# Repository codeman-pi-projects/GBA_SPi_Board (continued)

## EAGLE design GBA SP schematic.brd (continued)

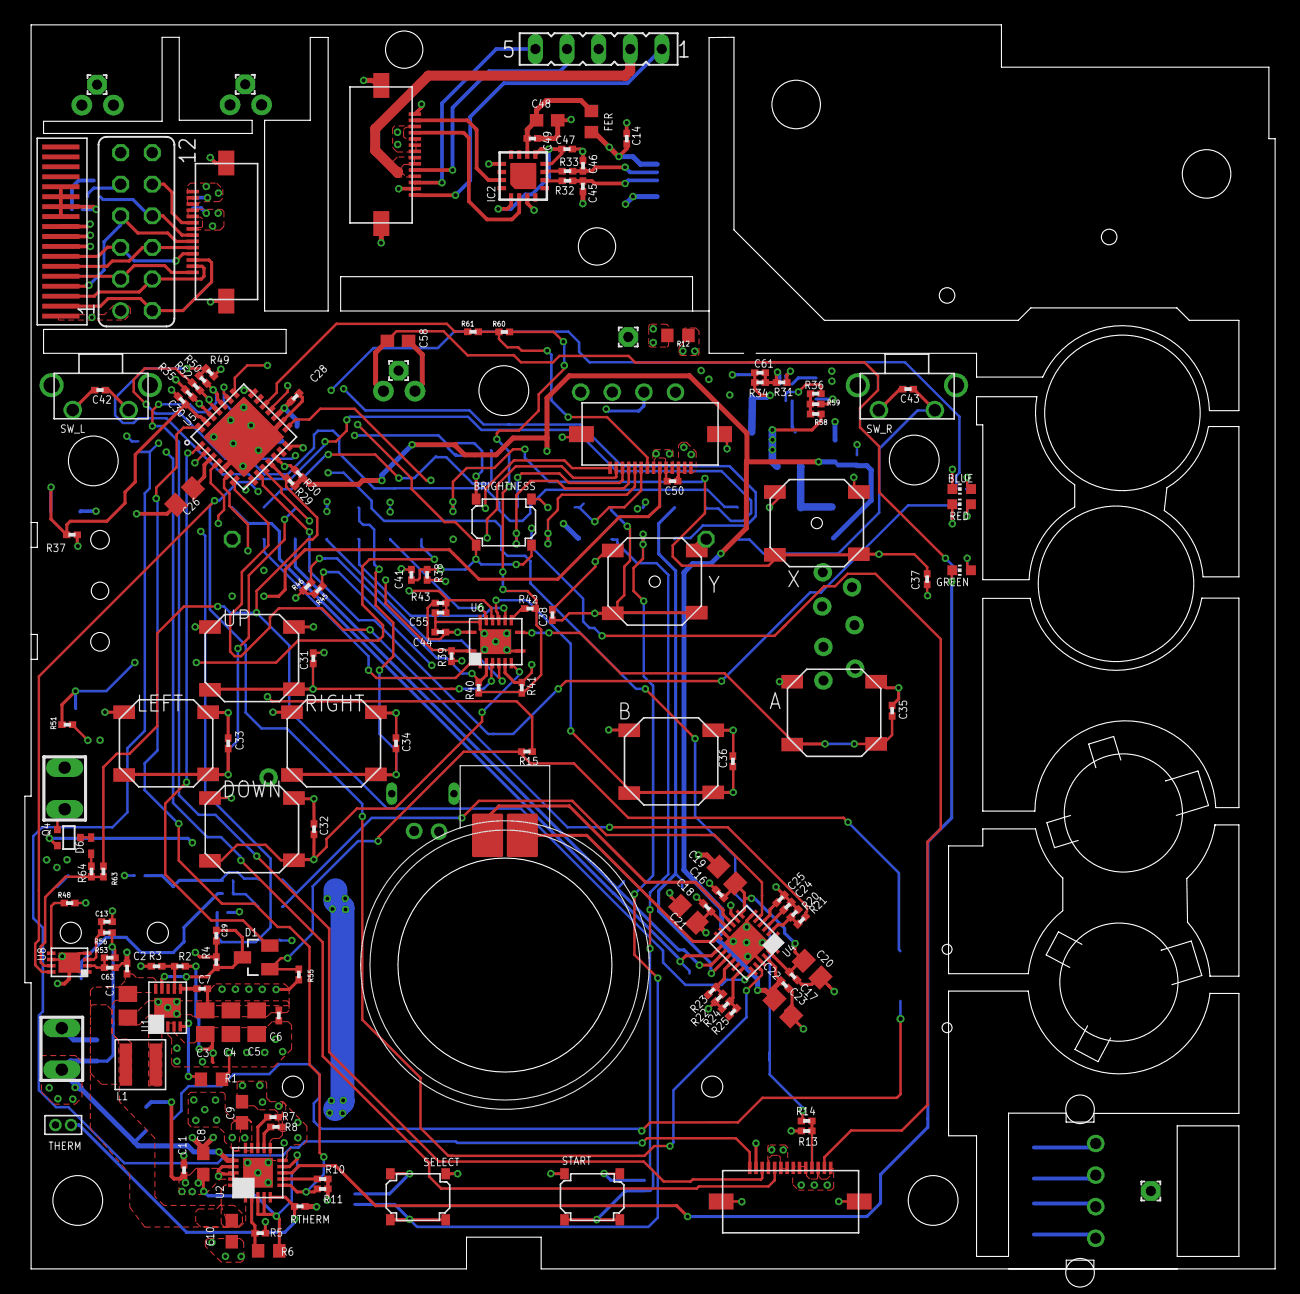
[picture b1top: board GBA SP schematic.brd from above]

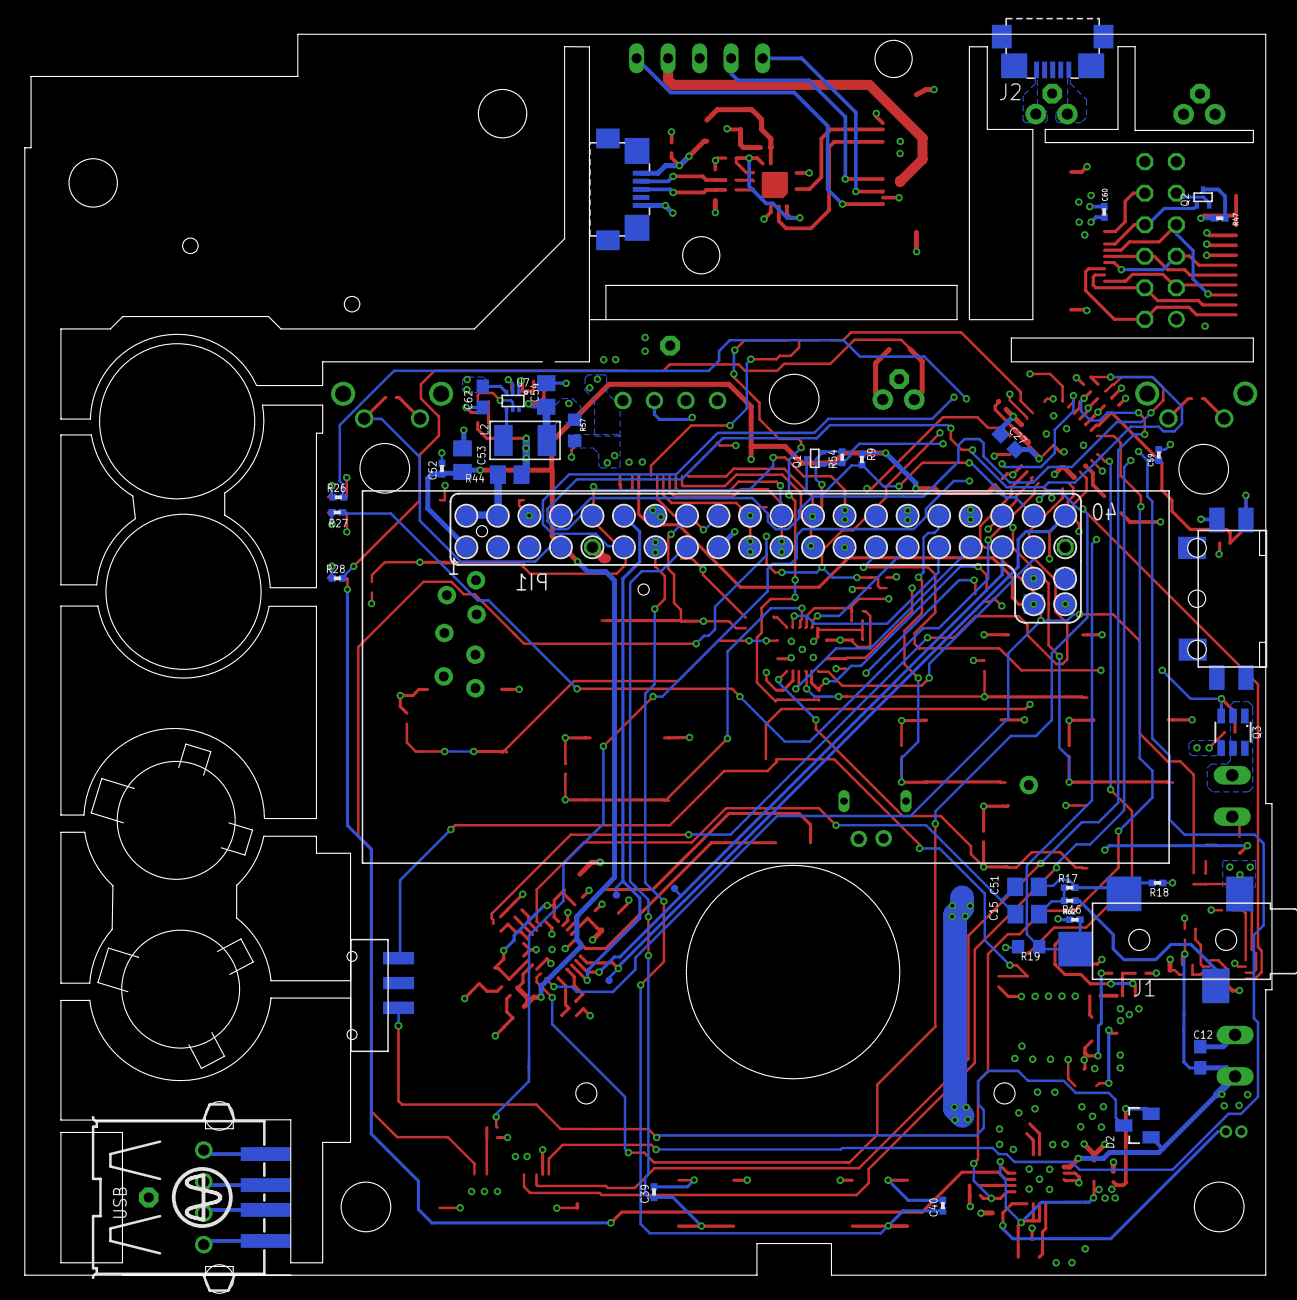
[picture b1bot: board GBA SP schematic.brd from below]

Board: 4 copper layers, 100.5 x 100.0 mm, 191 parts (40 on the bottom side), 139 nets.

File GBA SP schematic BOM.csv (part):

"Part";"Value";"Device";"Package";"Description";"DIGIKEY";"MF";"MOUSER";"MPN";"OC_FARNELL";"OC_NEWARK";"TP_SIGNAL_NAME";
"A";"TACTILEGBA_SP";"TACTILEGBA_SP";"GBA_SP_TACT";"";"";"ALPS";"";"SKRRAAE010";"";"";"";
"B";"TACTILEGBA_SP";"TACTILEGBA_SP";"GBA_SP_TACT";"";"";"ALPS";"688-SKRRAA";"SKRRAAE010";"";"";"";
"BATT";"DNP";"HEADER-1X2";"HEADER-1X2";"";"";"";"";"";"";"";"";
"BLUE";"";"LEDCHIP-LED0603";"CHIP-LED0603";"LED";"160-1827-1-ND";"Lite-On";"";"LTST-C193TBKT-5A";"";"";"";
"BRIGHTNESS";"TACTILE";"TACTILE";"TL3315";"";"EG4621CT-ND";"E-switch";"";"TL3315NF160Q";"";"";"";
"C1";"22uF";"C-USC0805";"C0805";"CAPACITOR, American symbol";"587-5464-1-ND";"Taiyo Yuden";"";"LMK212BBJ226MG-T";"";"";"";
"C2";"0.1uF";"C-US0402_REAL";"0402_REAL";"CAPACITOR, American symbol";"311-1343-1-ND";"Yageo";"";"CC0603ZRY5V9BB104";"";"";"";
"C3";"22uF";"C-USC0805";"C0805";"CAPACITOR, American symbol";"587-5464-1-ND";"Taiyo Yuden";"";"LMK212BBJ226MG-T";"";"";"";
"C4";"22uF";"C-USC0805";"C0805";"CAPACITOR, American symbol";"587-5464-1-ND";"Taiyo Yuden";"";"LMK212BBJ226MG-T";"";"";"";
"C5";"22uF";"C-USC0805";"C0805";"CAPACITOR, American symbol";"587-5464-1-ND";"Taiyo Yuden";"";"LMK212BBJ226MG-T";"";"";"";
"C6";"0.1uF";"C-US0402_REAL";"0402_REAL";"CAPACITOR, American symbol";"311-1343-1-ND";"Yageo";"";"CC0603ZRY5V9BB104";"";"";"";
"C7";"10nF";"C-US0402_REAL";"0402_REAL";"CAPACITOR, American symbol";"490-4516-1-ND";"Murata";"";"GRM155R71H103KA88D";"";"";"";
"C8";"4.7uF";"C-EUC0603";"C0603";"CAPACITOR, European symbol";"311-1455-1-ND";"Yageo";"";"CC0603KRX5R6BB475";"";"";"";
"C9";"4.7uF";"C-EUC0603";"C0603";"CAPACITOR, European symbol";"311-1455-1-ND";"Yageo";"";"CC0603KRX5R6BB475";"";"";"";
"C10";"4.7uF";"C-EUC0603";"C0603";"CAPACITOR, European symbol";"311-1455-1-ND";"Yageo";"";"CC0603KRX5R6BB475";"";"";"";
"C11";"0.1uF";"C-US0402_REAL";"0402_REAL";"CAPACITOR, American symbol";"311-1343-1-ND";"Yageo";"";"CC0603ZRY5V9BB104";"";"";"";
"C12";"4.7uF";"C-EUC0603";"C0603";"CAPACITOR, European symbol";"311-1455-1-ND";"Yageo";"";"CC0603KRX5R6BB475";"";"";"";
"C13";"0.1uF";"C-US0402_REAL";"0402_REAL";"CAPACITOR, American symbol";"490-4516-1-ND";"Murata";"";"GRM155R71H103KA88D";"";"";"";
"C14";"0.1uF";"C-EU0402_REAL";"0402_REAL";"CAPACITOR, European symbol";"311-1343-1-ND";"Yageo";"";"CC0603ZRY5V9BB104";"";"";"";
"C15";"47uF";"C-EUC0805";"C0805";"CAPACITOR, European symbol";"490-9961-1-ND";"Murata";"";"GRM21BR61A476ME15L";"";"";"";
"C16";"0.1uF";"C-US0402_REAL";"0402_REAL";"CAPACITOR, American symbol";"311-1343-1-ND";"Yageo";"";"CC0603ZRY5V9BB104";"";"";"";
"C17";"0.1uF";"C-US0402_REAL";"0402_REAL";"CAPACITOR, American symbol";"311-1343-1-ND";"Yageo";"";"CC0603ZRY5V9BB104";"";"";"";
"C18";"0.1uF";"C-US0402_REAL";"0402_REAL";"CAPACITOR, American symbol";"311-1343-1-ND";"Yageo";"";"CC0603ZRY5V9BB104";"";"";"";
"C19";"22uF";"C-EUC0805";"C0805";"CAPACITOR, European symbol";"1276-6504-1-ND";"Samsung";"";"CL10A226MPCNUBE";"";"";"";
"C20";"22uF";"C-EUC0805";"C0805";"CAPACITOR, European symbol";"1276-6504-1-ND";"Samsung";"";"CL10A226MPCNUBE";"";"";"";
"C21";"22uF";"C-EUC0805";"C0805";"CAPACITOR, European symbol";"1276-6504-1-ND";"Samsung";"";"CL10A226MPCNUBE";"";"";"";
"C22";"0.1uF";"C-US0402_REAL";"0402_REAL";"CAPACITOR, American symbol";"311-1343-1-ND";"Yageo";"";"CC0603ZRY5V9BB104";"";"";"";
"C23";"22uF";"C-EUC0805";"C0805";"CAPACITOR, European symbol";"1276-6504-1-ND";"Samsung";"";"CL10A226MPCNUBE";"";"";"";
"C24";"0.1uF";"C-US0402_REAL";"0402_REAL";"CAPACITOR, American symbol";"311-1343-1-ND";"Yageo";"";"CC0603ZRY5V9BB104";"";"";"";
"C25";"0.1uF";"C-US0402_REAL";"0402_REAL";"CAPACITOR, American symbol";"311-1343-1-ND";"Yageo";"";"CC0603ZRY5V9BB104";"";"";"";
"C26";"22uF";"C-EUC0805";"C0805";"CAPACITOR, European symbol";"1276-6504-1-ND";"Samsung";"";"CL10A226MPCNUBE";"";"";"";
"C27";"4.7uF";"C-EUC0603";"C0603";"CAPACITOR, European symbol";"1276-6504-1-ND";"Samsung";"";"CL10A226MPCNUBE";"";"";"";
"C28";"0.1uF";"C-US0402_REAL";"0402_REAL";"CAPACITOR, American symbol";"311-1343-1-ND";"Yageo";"";"CC0603ZRY5V9BB104";"";"";"";
"C29";"0.1uF";"C-US0402_REAL";"0402_REAL";"CAPACITOR, American symbol";"311-1343-1-ND";"Yageo";"";"CC0603ZRY5V9BB104";"";"";"";
"C30";"0.1uF";"C-US0402_REAL";"0402_REAL";"CAPACITOR, American symbol";"311-1343-1-ND";"Yageo";"";"CC0603ZRY5V9BB104";"";"";"";
"C31";"0.1uF";"C-US0402_REAL";"0402_REAL";"CAPACITOR, American symbol";"311-1343-1-ND";"Yageo";"";"CC0603ZRY5V9BB104";"";"";"";
"C32";"0.1uF";"C-US0402_REAL";"0402_REAL";"CAPACITOR, American symbol";"311-1343-1-ND";"Yageo";"";"CC0603ZRY5V9BB104";"";"";"";
"C33";"0.1uF";"C-US0402_REAL";"0402_REAL";"CAPACITOR, American symbol";"311-1343-1-ND";"Yageo";"";"CC0603ZRY5V9BB104";"";"";"";
"C34";"0.1uF";"C-US0402_REAL";"0402_REAL";"CAPACITOR, American symbol";"311-1343-1-ND";"Yageo";"";"CC0603ZRY5V9BB104";"";"";"";
"C35";"0.1uF";"C-US0402_REAL";"0402_REAL";"CAPACITOR, American symbol";"311-1343-1-ND";"Yageo";"";"CC0603ZRY5V9BB104";"";"";"";
"C36";"0.1uF";"C-US0402_REAL";"0402_REAL";"CAPACITOR, American symbol";"311-1343-1-ND";"Yageo";"";"CC0603ZRY5V9BB104";"";"";"";
"C37";"0.1uF";"C-US0402_REAL";"0402_REAL";"CAPACITOR, American symbol";"311-1343-1-ND";"Yageo";"";"CC0603ZRY5V9BB104";"";"";"";
"C38";"0.1uF";"C-US0402_REAL";"0402_REAL";"CAPACITOR, American symbol";"311-1343-1-ND";"Yageo";"";"CC0603ZRY5V9BB104";"";"";"";
"C39";"0.1uF";"C-US0402_REAL";"0402_REAL";"CAPACITOR, American symbol";"311-1343-1-ND";"Yageo";"";"CC0603ZRY5V9BB104";"";"";"";
"C40";"0.1uF";"C-US0402_REAL";"0402_REAL";"CAPACITOR, American symbol";"311-1343-1-ND";"Yageo";"";"CC0603ZRY5V9BB104";"";"";"";
"C41";"0.1uF";"C-US0402_REAL";"0402_REAL";"CAPACITOR, American symbol";"311-1343-1-ND";"Yageo";"";"CC0603ZRY5V9BB104";"";"";"";
"C42";"0.1uF";"C-US0402_REAL";"0402_REAL";"CAPACITOR, American symbol";"311-1343-1-ND";"Yageo";"";"CC0603ZRY5V9BB104";"";"";"";
"C43";"0.1uF";"C-US0402_REAL";"0402_REAL";"CAPACITOR, American symbol";"311-1343-1-ND";"Yageo";"";"CC0603ZRY5V9BB104";"";"";"";
"C44";"0.1uF";"C-US0402_REAL";"0402_REAL";"CAPACITOR, American symbol";"311-1343-1-ND";"Yageo";"";"CC0603ZRY5V9BB104";"";"";"";
"C45";"33pF";"C-EU0402_REAL";"0402_REAL";"CAPACITOR, European symbol";"";"";"";"";"";"";"";
"C46";"33pF";"C-EU0402_REAL";"0402_REAL";"CAPACITOR, European symbol";"";"";"";"";"";"";"";
"C47";"0.1uF";"C-EU0402_REAL";"0402_REAL";"CAPACITOR, European symbol";"311-1343-1-ND";"Yageo";"";"CC0603ZRY5V9BB104";"";"";"";
"C48";"4.7uF";"C-EUC0603";"C0603";"CAPACITOR, European symbol";"311-1455-1-ND";"Yageo";"";"CC0603KRX5R6BB475";"";"";"";
"C49";"0.1uF";"C-EU0402_REAL";"0402_REAL";"CAPACITOR, European symbol";"311-1343-1-ND";"Yageo";"";"CC0603ZRY5V9BB104";"";"";"";
"C50";"0.1uF";"C-US0402_REAL";"0402_REAL";"CAPACITOR, American symbol";"311-1343-1-ND";"Yageo";"";"CC0603ZRY5V9BB104";"";"";"";
"C51";"DNP";"C-EUC0805";"C0805";"CAPACITOR, European symbol";"490-9961-1-ND";"Murata";"";"GRM21BR61A476ME15L";"";"";"";
"C52";"0.1uF";"C-US0402_REAL";"0402_REAL";"CAPACITOR, American symbol";"311-1343-1-ND";"Yageo";"";"CC0603ZRY5V9BB104";"";"";"";
"C53";"22uF";"C-EUC0805";"C0805";"CAPACITOR, European symbol";"1276-6504-1-ND";"Samsung";"";"CL10A226MPCNUBE";"";"";"";
"C54";"22uF";"C-EUC0805";"C0805";"CAPACITOR, European symbol";"1276-6504-1-ND";"Samsung";"";"CL10A226MPCNUBE";"";"";"";
"C55";"0.1uF";"C-US0402_REAL";"0402_REAL";"CAPACITOR, American symbol";"311-1343-1-ND";"Yageo";"";"CC0603ZRY5V9BB104";"";"";"";
"C58";"4.7uF";"C-EUC0603";"C0603";"CAPACITOR, European symbol";"311-1455-1-ND";"Yageo";"";"CC0603KRX5R6BB475";"";"";"";
"C59";"0.1uF";"C-US0402_REAL";"0402_REAL";"CAPACITOR, American symbol";"311-1343-1-ND";"Yageo";"";"CC0603ZRY5V9BB104";"";"";"";
"C60";"0.1uF";"C-US0402_REAL";"0402_REAL";"CAPACITOR, American symbol";"311-1343-1-ND";"Yageo";"";"CC0603ZRY5V9BB104";"";"";"";
"C61";"6.8pF";"C-EU0402_REAL";"0402_REAL";"CAPACITOR, European symbol";"311-1637-1-ND";"Yageo";"";"CC0402DRNPO9BN6R8";"";"";"";
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
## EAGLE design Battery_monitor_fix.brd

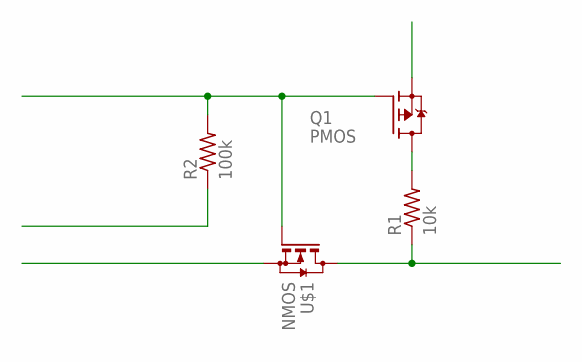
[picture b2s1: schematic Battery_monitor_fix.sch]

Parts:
Q1: PMOS; SC70
R1: 10k; 0402_REAL
R2: 100k; 0402_REAL
U$1: NMOS; SC70

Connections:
unnamed: Q1.G, R2.2, U$1.G
unnamed: Q1.D, R1.2
unnamed: R1.1, U$1.D

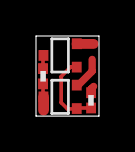
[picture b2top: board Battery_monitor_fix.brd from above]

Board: 2 copper layers, 3.5 x 4.5 mm, 4 parts (0 on the bottom side), 3 nets.

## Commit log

2018-06-28 adding board files
2018-06-28 updating BOM
2018-06-29 fixing BOM
2018-07-06 mounting holes, fixed volume circuit
2018-07-10 added volume slider holes
2018-07-13 finishing board files
2018-08-13 schematic pdf
2018-10-26 battery monitor fix
2018-10-27 Pull-up for battery monitor
